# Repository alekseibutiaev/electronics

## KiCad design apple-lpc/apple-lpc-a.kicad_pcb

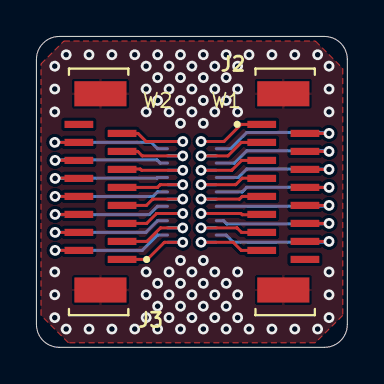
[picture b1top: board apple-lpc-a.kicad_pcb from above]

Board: 2 copper layers, 17.3 x 17.3 mm, 3 parts (1 on the bottom side), 31 nets.

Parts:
J1: DF40C-30DP-0.4V; HRS_DF40C-30DP-0.4V_51_
J2: ODD; TE_1-1734742-6
J3: EVEN; TE_1-1734742-6

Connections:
/W1: J1.1, J2.1
/W2: J1.2, J3.15
/W3: J1.3, J2.2
/W4: J1.4, J3.14
/W5: J1.5, J2.3
/W6: J1.6, J3.13
/W7: J1.7, J2.4
/W8: J1.8, J3.12
/W9: J1.9, J2.5
/W10: J1.10, J3.11
/W11: J1.11, J2.6
/W12: J1.12, J3.10
/W13: J1.13, J2.7
/W14: J1.14, J3.9
/W15: J1.15, J2.8
/W16: J1.16, J3.8
/W17: J1.17, J2.9
/W18: J1.18, J3.7
/W19: J1.19, J2.10
/W20: J1.20, J3.6
/W21: J1.21, J2.11
/W22: J1.22, J3.5
/W23: J1.23, J2.12
/W24: J1.24, J3.4
/W25: J1.25, J2.13
/W26: J1.26, J3.3
/W27: J1.27, J2.14
/W28: J1.28, J3.2
/W29: J1.29, J2.15
/W30: J1.30, J3.1
GND: J1.S1 (S2), J1.S2 (S3), J1.S3 (S4), J1.S4 (S1), J2.S1, J2.S2, J3.S1, J3.S2

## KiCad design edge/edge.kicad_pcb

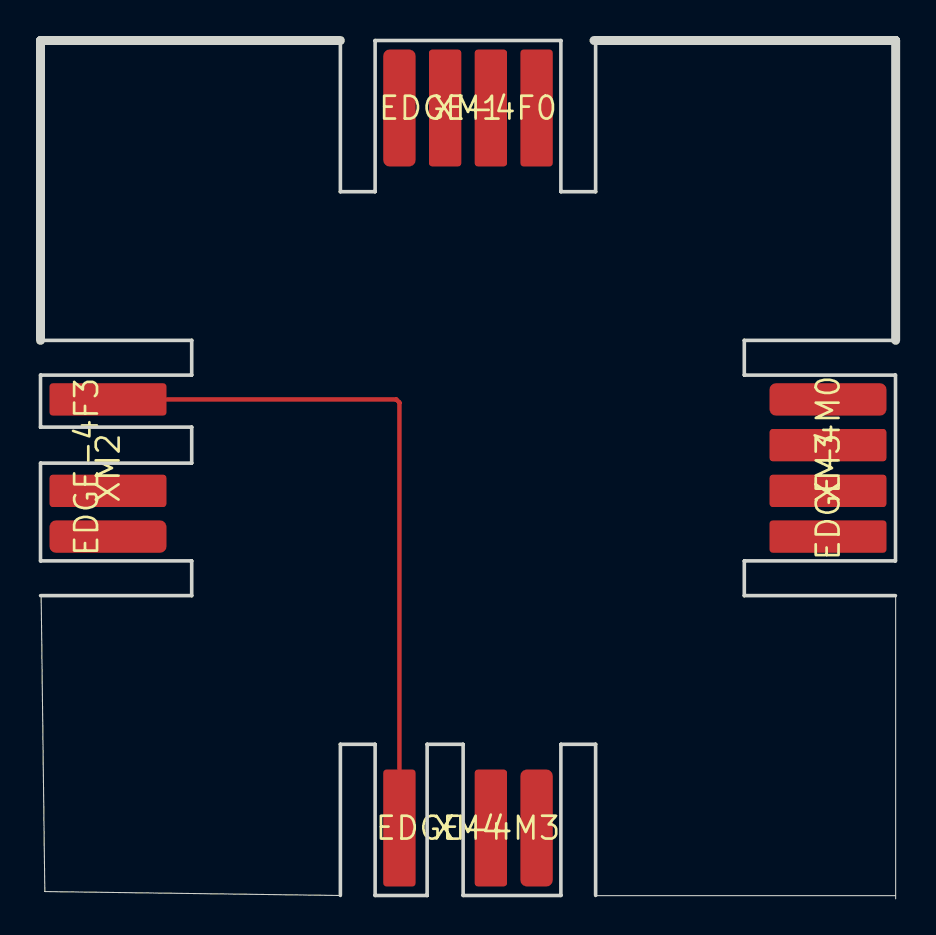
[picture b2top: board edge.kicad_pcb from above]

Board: 2 copper layers, 47.5 x 47.7 mm, 4 parts (0 on the bottom side), 14 nets.

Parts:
XM1: EDGE-4F0; EDGE_4M0-2.54
XM2: EDGE-4F3; EDGE_4M3-2.54
XM3: EDGE-4M0; EDGE_4M0-2.54
XM4: EDGE-4M3; EDGE_4M3-2.54

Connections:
/MA1: XM1.A1, XM3.A1
/MA2: XM1.A2, XM3.A2
/MA3: XM1.A3, XM3.A3
/MA4: XM1.A4, XM3.A4
/MB1: XM2.A1, XM4.A1
/MB2: XM2.A2, XM4.A2
/MB3: XM2.A4, XM4.A4
/MC1: XM1.B1, XM3.B1
/MC2: XM1.B2, XM3.B2
/MC3: XM1.B3, XM3.B3
/MC4: XM1.B4, XM3.B4
/MD1: XM2.B1, XM4.B1
/MD2: XM2.B2, XM4.B2
/MD3: XM2.B4, XM4.B4

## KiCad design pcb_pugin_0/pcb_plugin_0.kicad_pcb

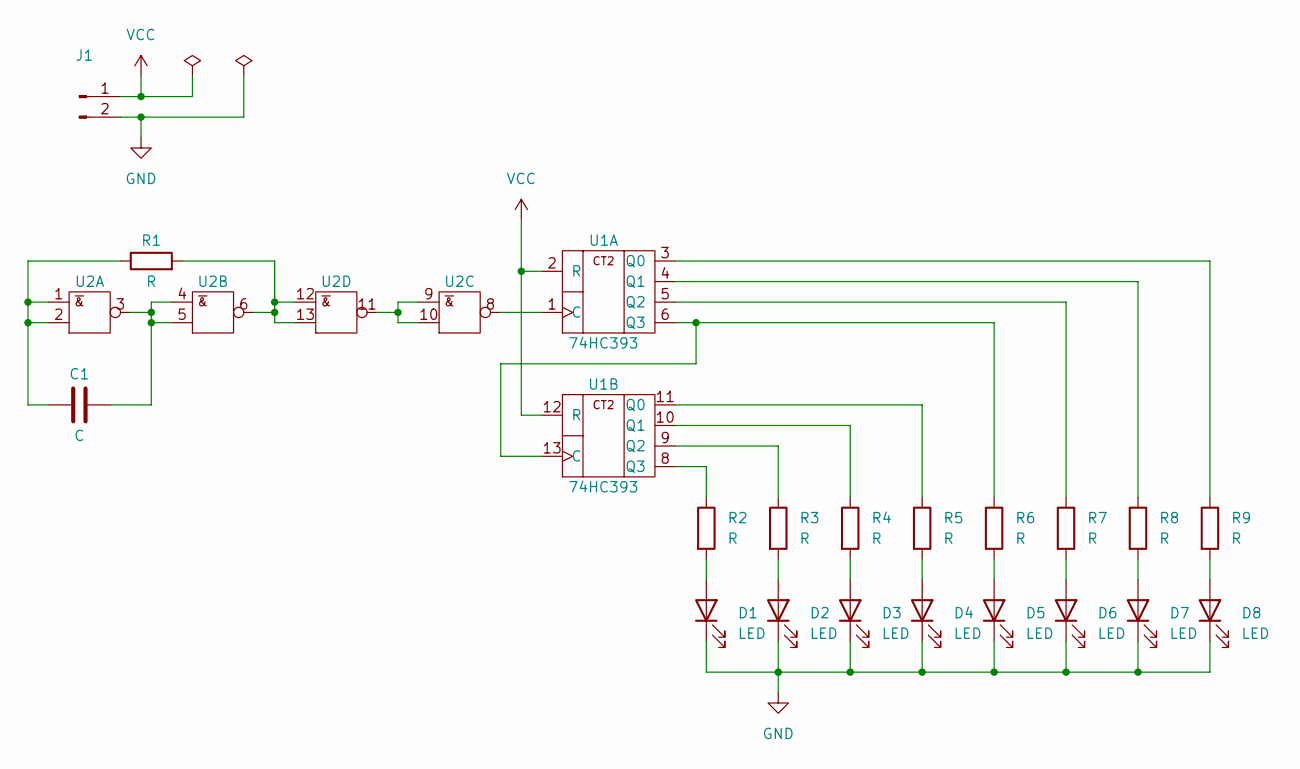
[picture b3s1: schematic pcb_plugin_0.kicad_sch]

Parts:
C1: C; C_0805_2012Metric_Pad1.18x1.45mm_HandSolder
D1, D2, D3, D4, D5, D6, D7, D8: LED; D_0805_2012Metric_Pad1.15x1.40mm_HandSolder
J1: Conn_01x02_Male; PinHeader_1x02_P2.54mm_Horizontal
R1, R2, R3, R4, R5, R6, R7, R8, R9: R; R_0805_2012Metric_Pad1.20x1.40mm_HandSolder
U1: 74HC393; DIP-14_W7.62mm
U2: (no value)

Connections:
GND: D1.1 (K), D2.1 (K), D3.1 (K), D4.1 (K), D5.1 (K), D6.1 (K), D7.1 (K), D8.1 (K), J1.2, U1.7 (GND), U2.7 (GND)
unnamed: C1.1, R1.1, U2.1 (A), U2.2 (B)
unnamed: C1.2, U2.3 (~Y), U2.4 (A), U2.5 (B)
unnamed: D1.2 (A), R2.2
unnamed: D2.2 (A), R3.2
unnamed: D3.2 (A), R4.2
unnamed: D4.2 (A), R5.2
unnamed: D5.2 (A), R6.2
unnamed: D6.2 (A), R7.2
unnamed: D7.2 (A), R8.2
unnamed: D8.2 (A), R9.2
unnamed: R1.2, U2.6 (~Y), U2.12 (A), U2.13 (B)
unnamed: R2.1, U1.8 (Q3)
unnamed: R3.1, U1.9 (Q2)
unnamed: R4.1, U1.10 (Q1)
unnamed: R5.1, U1.11 (Q0)
unnamed: R6.1, U1.6 (Q3), U1.13 (C)
unnamed: R7.1, U1.5 (Q2)
unnamed: R8.1, U1.4 (Q1)
unnamed: R9.1, U1.3 (Q0)
unnamed: U1.1 (C), U2.8 (~Y)
unnamed: U2.9 (A), U2.10 (B), U2.11 (~Y)
VCC: J1.1, U1.2 (R), U1.12 (R), U1.14 (VCC), U2.14 (VCC)

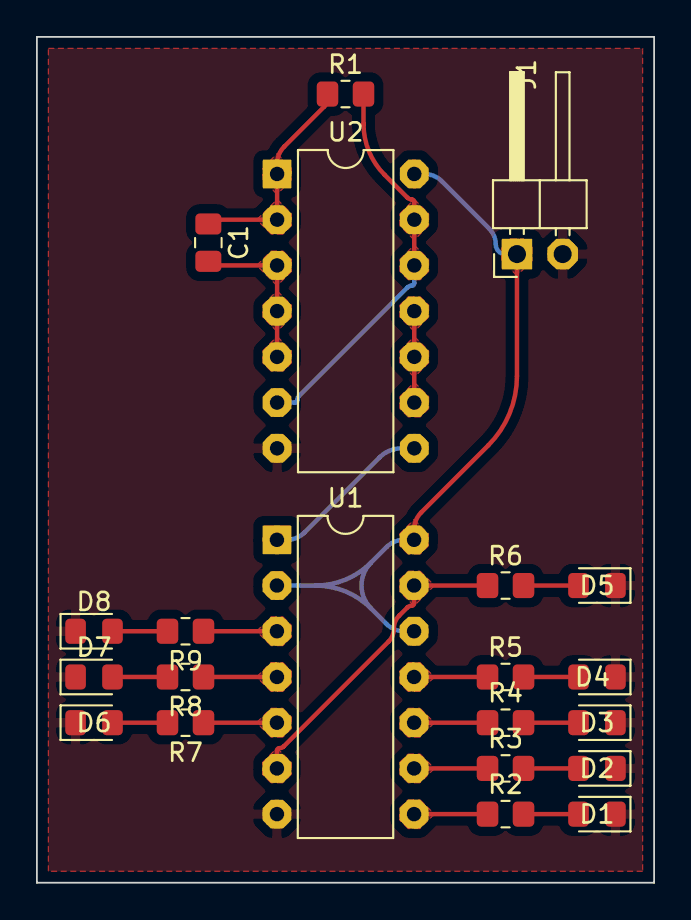
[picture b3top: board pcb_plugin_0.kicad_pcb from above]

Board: 2 copper layers, 34.3 x 47.0 mm, 21 parts (0 on the bottom side), 23 nets.

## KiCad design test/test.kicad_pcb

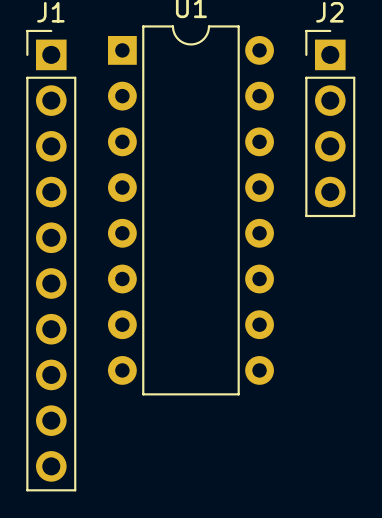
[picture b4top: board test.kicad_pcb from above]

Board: 2 copper layers, 3 parts (0 on the bottom side), 14 nets, no tracks yet.

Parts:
J1: Conn_01x10_Male; PinHeader_1x10_P2.54mm_Vertical
J2: Conn_01x04_Male; PinHeader_1x04_P2.54mm_Vertical
U1: 74HC157; DIP-16_W7.62mm

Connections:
unnamed: J1.1, U1.15 (~G)
unnamed: J1.2, U1.2 (A0)
unnamed: J1.3, U1.3 (B0)
unnamed: J1.4, U1.5 (A1)
unnamed: J1.5, U1.6 (B1)
unnamed: J1.6, U1.11 (A2)
unnamed: J1.7, U1.10 (B2)
unnamed: J1.8, U1.14 (A3)
unnamed: J1.9, U1.13 (B3)
unnamed: J1.10, U1.1 (~A/B)
unnamed: J2.1, U1.4 (Y0)
unnamed: J2.2, U1.7 (Y1)
unnamed: J2.3, U1.9 (Y2)
unnamed: J2.4, U1.12 (Y3)

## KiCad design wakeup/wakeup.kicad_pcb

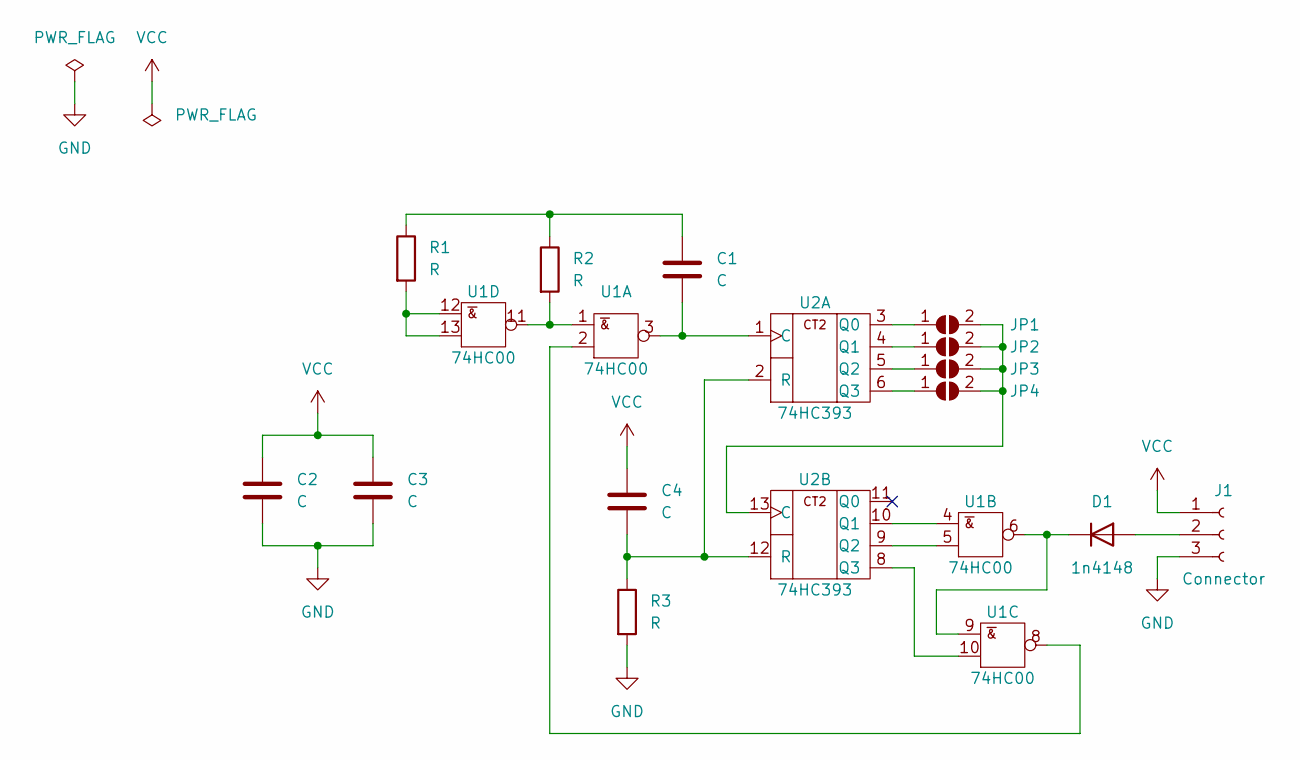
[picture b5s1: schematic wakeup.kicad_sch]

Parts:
C1, C2, C3, C4: C; C_0805_2012Metric_Pad1.18x1.45mm_HandSolder
D1: 1n4148
J1: Connector; PinSocket_1x03_P2.54mm_Vertical
JP1, JP2, JP3, JP4: DEV1; SolderJumper-2_P1.3mm_Open_RoundedPad1.0x1.5mm
R1, R2, R3: R; R_0805_2012Metric_Pad1.20x1.40mm_HandSolder
U1: 74HC00; SO-14_3.9x8.65mm_P1.27mm
U2: 74HC393; SO-14_3.9x8.65mm_P1.27mm

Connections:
GND: C2.2, C3.2, J1.3, R3.2, U1.7 (GND), U2.7 (GND)
unnamed: C1.1, R1.1, R2.1
unnamed: C1.2, U1.3 (~Y), U2.1 (C)
unnamed: C4.2, R3.1, U2.2 (R), U2.12 (R)
unnamed: D1.1 (K), U1.6 (~Y), U1.9 (A)
unnamed: D1.2 (A), J1.2
unnamed: JP1.1 (A), U2.3 (Q0)
unnamed: JP1.2 (B), JP2.2 (B), JP3.2 (B), JP4.2 (B), U2.13 (C)
unnamed: JP2.1 (A), U2.4 (Q1)
unnamed: JP3.1 (A), U2.5 (Q2)
unnamed: JP4.1 (A), U2.6 (Q3)
unnamed: R1.2, U1.12 (A), U1.13 (B)
unnamed: R2.2, U1.1 (A), U1.11 (~Y)
unnamed: U1.2 (B), U1.8 (~Y)
unnamed: U1.4 (A), U2.10 (Q1)
unnamed: U1.5 (B), U2.9 (Q2)
unnamed: U1.10 (B), U2.8 (Q3)
VCC: C2.1, C3.1, C4.1, J1.1, U1.14 (VCC), U2.14 (VCC)

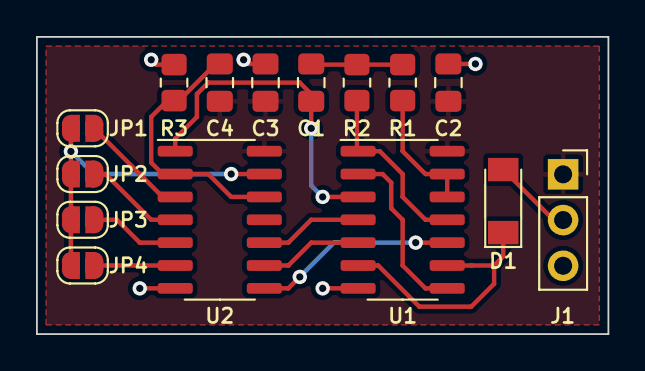
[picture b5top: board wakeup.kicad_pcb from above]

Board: 2 copper layers, 31.8 x 16.5 mm, 15 parts (0 on the bottom side), 18 nets.

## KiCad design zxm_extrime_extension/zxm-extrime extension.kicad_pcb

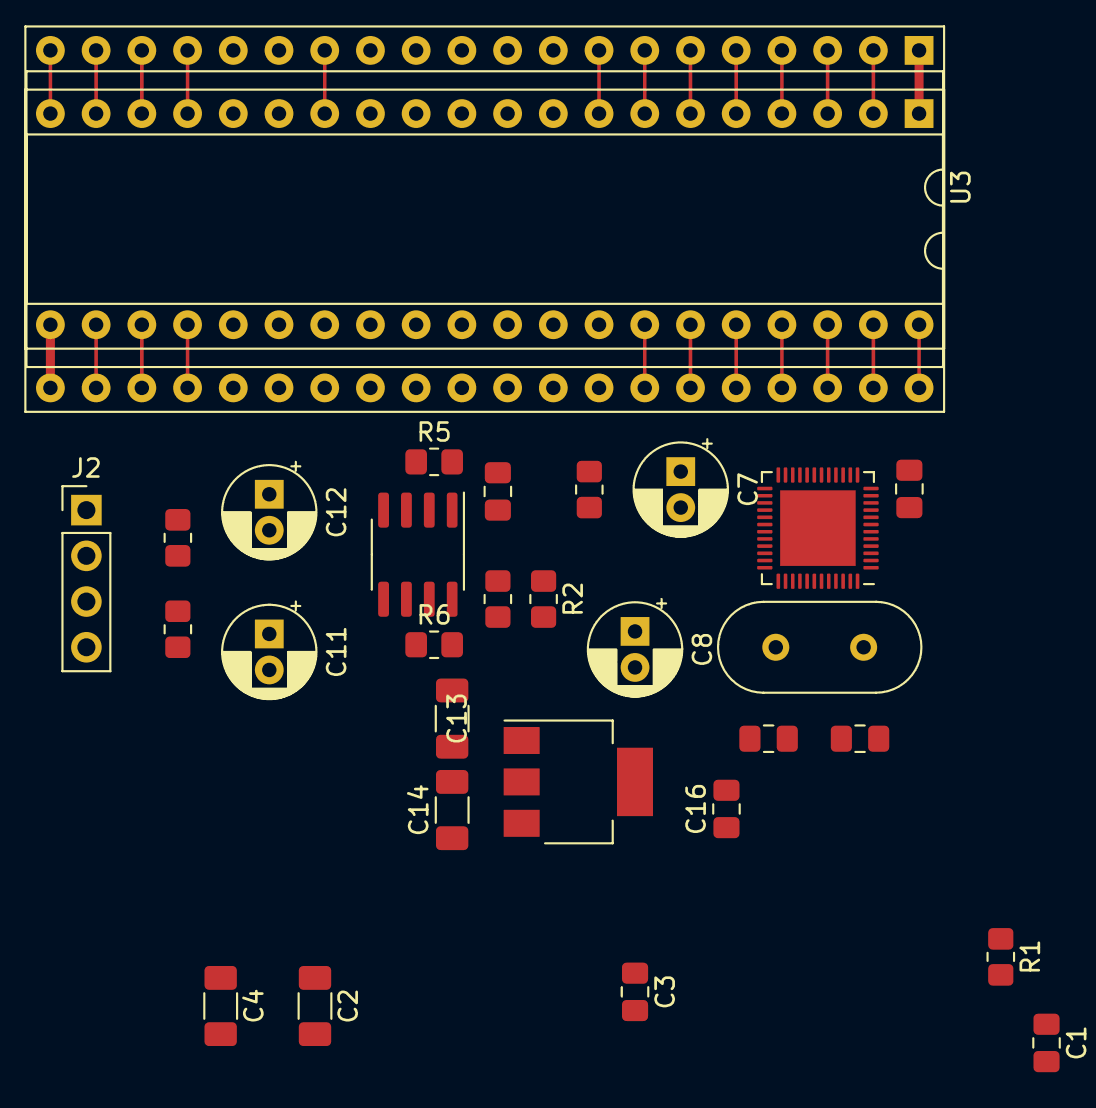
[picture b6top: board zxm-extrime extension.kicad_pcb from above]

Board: 2 copper layers, 30 parts (0 on the bottom side), 39 nets.

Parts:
C1, C3, C10, C15, C16: 100n; C_0805_2012Metric_Pad1.18x1.45mm_HandSolder
C2, C4, C13, C14: 10u; C_1206_3216Metric_Pad1.33x1.80mm_HandSolder
C5, C6: 22p; C_0805_2012Metric_Pad1.18x1.45mm_HandSolder
C7, C8, C11, C12: 10u; CP_Radial_D5.0mm_P2.00mm
J1: YM2203_Conn; DIP-40_W15.24mm_Socket
J2: Conn_01x04; PinHeader_1x04_P2.54mm_Vertical
R1, R2: 10k; R_0805_2012Metric_Pad1.20x1.40mm_HandSolder
R3, R7, R8: 47k; R_0805_2012Metric_Pad1.20x1.40mm_HandSolder
R4: 27k; R_0805_2012Metric_Pad1.20x1.40mm_HandSolder
R5, R6: 10K; R_0805_2012Metric_Pad1.20x1.40mm_HandSolder
U1: LM358D; SOIC-8_3.9x4.9mm_P1.27mm
U2: SAM2695; QFN-48-1EP_6x6mm_P0.4mm_EP4.2x4.2mm
U3: YM2203; DIP-40_W15.24mm_Socket
U4: 1117-3.3; SOT-223-3_TabPin2
ZQ1: 12MHz; Crystal_HC49-U_Vertical

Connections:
+3.3V: C14.1, C15.1, C16.1, U2.6 (VA33), U2.8 (VD33), U2.11 (VD33), U2.12 (~WR), U2.20 (VD33), U2.31 (VD33), U2.35 (VD33), U2.41 (VD33), U2.46 (VD33), U2.47 (XDIV), U4.2 (VO)
+5VA: C13.1, J1.21, R3.2, U1.8 (V+), U3.21 (VDD), U4.3 (VI)
/A: J1.20, U3.20 (A)
/A0: J1.37, U3.37 (A0)
/B: J1.19, U3.19 (B)
/C: J1.18, U3.18 (C)
/D0: J1.40, U3.40 (D0)
/D1: J1.2, U3.2 (D1)
/D2: J1.3, U3.3 (D2)
/D3: J1.4, U3.4 (D3)
/D4: J1.5, U3.5 (D4)
/D5: J1.6, U3.6 (D5)
/D6: J1.7, U3.7 (D6)
/D7: J1.8, U3.8 (D7)
/IOA2: J1.14, U2.16 (MIDI_IN), U3.14 (IOA2)
/M: J1.38, U3.38 (M)
/OP-O: J1.23, U3.23 (OP-O)
/SH: J1.22, J1.39, U3.22 (SH), U3.39 (S)
//CS: J1.34, U3.34 (~CS)
//RD: J1.36, U3.36 (~RD)
//RES: J1.24, U2.38 (~RST/~PD), U3.24 (~IC)
//WR: J1.35, U3.35 (~WR)
GND: C1.2, C2.2, C3.2, C4.2, C5.2, C6.1, C13.2, C14.2, C15.2, C16.2, J1.1, U2.9 (GND), U2.10 (A0), U2.13 (GND), U2.14 (~CS), U2.15 (~RD), U2.18 (GND), U2.25 (GND), U2.36 (GND), U2.45 (GND), U2.48 (GND), U2.49 (GND), U3.1 (GND), U4.1 (GND)
GNDA: C10.1, J1.17, J2.2, J2.3, R4.2, R7.1, R8.1, U1.4 (V-), U2.4 (AGND), U2.7 (MICIN), U3.17 (AGND)
unnamed: C7.2, R1.2
unnamed: C8.2, R2.2
unnamed: C11.1, R5.2, U1.1
unnamed: C12.1, R6.2, U1.7
unnamed: C12.2, J2.1, R8.2
unnamed: C11.2, J2.4, R7.2
unnamed: C10.2, R3.1, R4.1, U1.3 (+), U1.5 (+)
unnamed: R1.1, R5.1, U1.2 (-)
unnamed: R2.1, R6.1, U1.6 (-)
unnamed: C7.1, U2.1 (AOUTL)
unnamed: C8.1, U2.2 (AOUTR)
unnamed: C3.1, C4.1, U2.34 (OUTVC12)
unnamed: C1.1, C2.1, U2.5 (VCM)
unnamed: C5.1, U2.39 (X1), ZQ1.1
unnamed: C6.2, U2.40 (X2), ZQ1.2
